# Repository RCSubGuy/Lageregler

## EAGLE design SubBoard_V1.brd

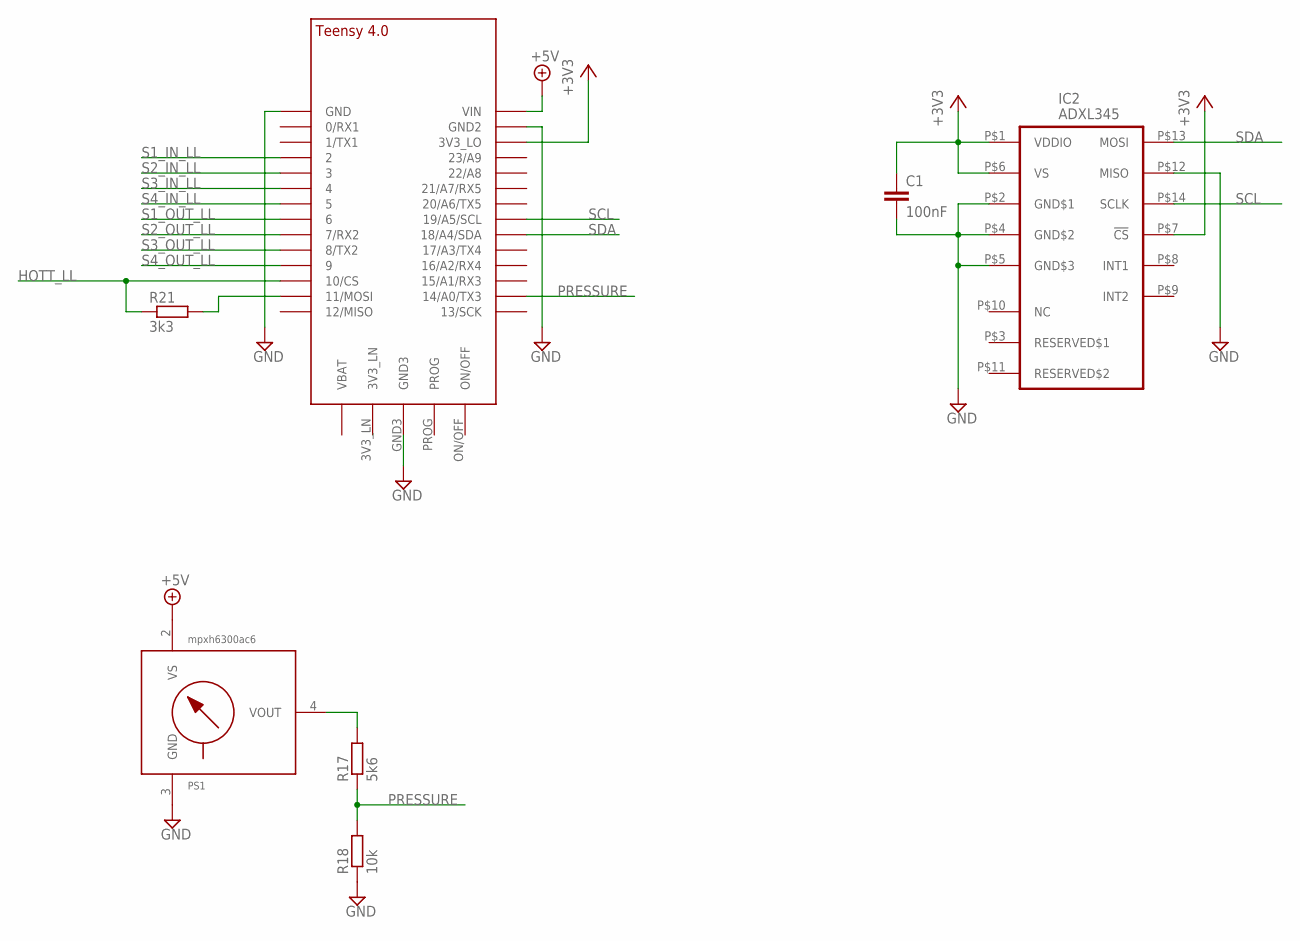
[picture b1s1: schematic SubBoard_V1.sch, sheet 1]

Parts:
C1: 100nF; C0805
IC2: ADXL345; LGA14
M1: TEENSY_4.0-BASIC
PS1: mpxh6300ac6; 482A
R17: 5k6; R0805
R18: 10k; R0805
R21: 3k3; R0805

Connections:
+3V3: C1.1, IC2.P$1 (VDDIO), IC2.P$6 (VS), IC2.P$7 (!CS), M1.3V3_LO; also elsewhere on the board
+5V: M1.VIN, PS1.2 (VS); also elsewhere on the board
GND: C1.2, IC2.P$2 (GND$1), IC2.P$4 (GND$2), IC2.P$5 (GND$3), IC2.P$12 (MISO), M1.GND, M1.GND2, M1.GND3, PS1.3 (GND), R18.1; also elsewhere on the board
HOTT_LL: M1.10/CS, R21.1; also elsewhere on the board
unnamed: PS1.4 (VOUT), R17.2
unnamed: M1.11/MOSI, R21.2
PRESSURE: M1.14/A0 (14/A0/TX3), R17.1, R18.2
S1_IN_LL: M1.2; also elsewhere on the board
S1_OUT_LL: M1.6; also elsewhere on the board
S2_IN_LL: M1.3/CANTX (3); also elsewhere on the board
S2_OUT_LL: M1.7 (7/RX2); also elsewhere on the board
S3_IN_LL: M1.4/CANRX (4); also elsewhere on the board
S3_OUT_LL: M1.8 (8/TX2); also elsewhere on the board
S4_IN_LL: M1.5; also elsewhere on the board
S4_OUT_LL: M1.9/CS (9); also elsewhere on the board
SCL: IC2.P$14 (SCLK), M1.19/A5/SCL
SDA: IC2.P$13 (MOSI), M1.18/A4/SDA

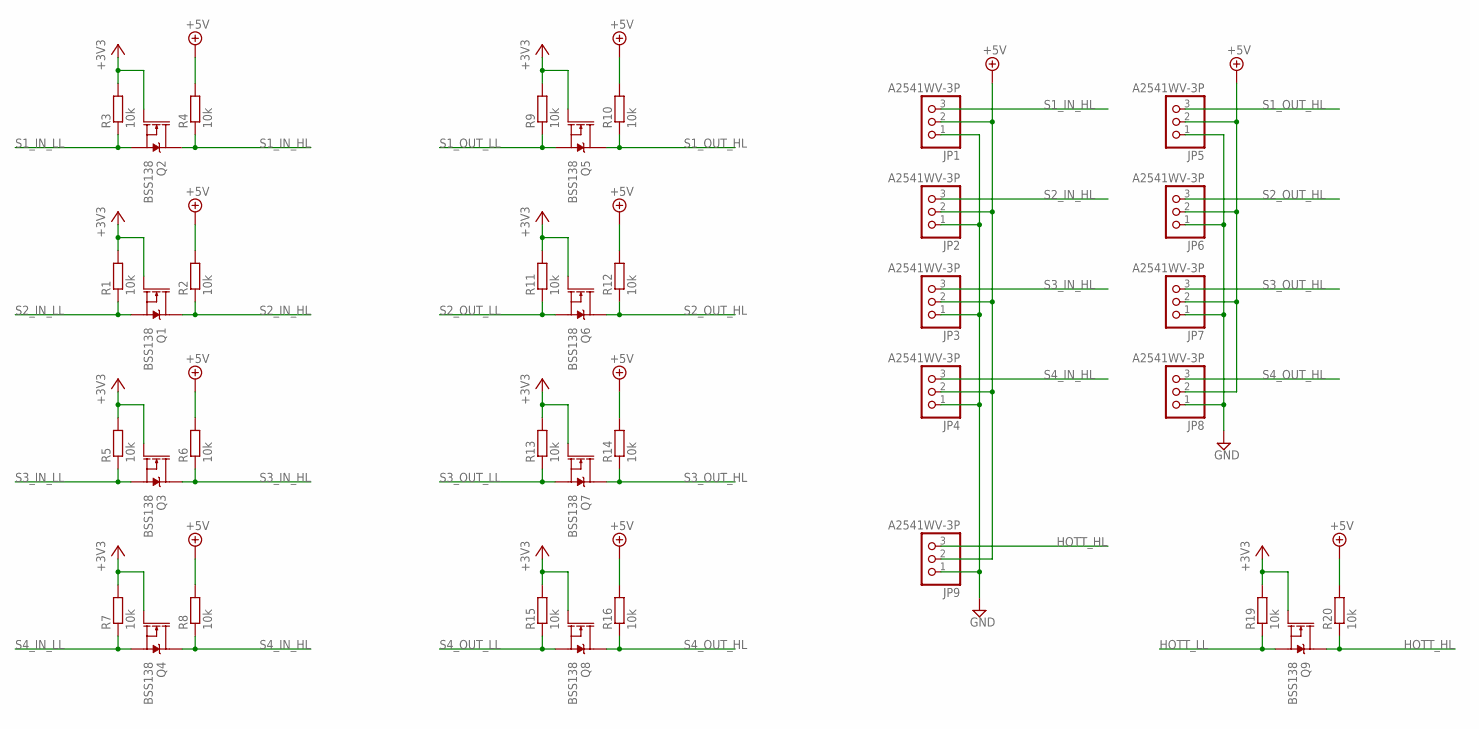
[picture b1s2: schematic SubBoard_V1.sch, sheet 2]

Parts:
JP1, JP2, JP3, JP4, JP5, JP6, JP7, JP8, JP9: A2541WV-3P; 1X03
Q1, Q2, Q3, Q4, Q5, Q6, Q7, Q8, Q9: BSS138; SOT23-3
R1, R2, R3, R4, R5, R6, R7, R8, R9, R10, R11, R12, R13, R14, R15, R16, R19, R20: 10k; R0603

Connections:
+3V3: Q1.1 (G), Q2.1 (G), Q3.1 (G), Q4.1 (G), Q5.1 (G), Q6.1 (G), Q7.1 (G), Q8.1 (G), Q9.1 (G), R1.2, R3.2, R5.2, R7.2, R9.2, R11.2, R13.2, R15.2, R19.2; also elsewhere on the board
+5V: JP1.2, JP2.2, JP3.2, JP4.2, JP5.2, JP6.2, JP7.2, JP8.2, JP9.2, R2.2, R4.2, R6.2, R8.2, R10.2, R12.2, R14.2, R16.2, R20.2; also elsewhere on the board
GND: JP1.1, JP2.1, JP3.1, JP4.1, JP5.1, JP6.1, JP7.1, JP8.1, JP9.1; also elsewhere on the board
HOTT_HL: JP9.3, Q9.3 (D), R20.1
HOTT_LL: Q9.2 (S), R19.1; also elsewhere on the board
S1_IN_HL: JP1.3, Q2.3 (D), R4.1
S1_IN_LL: Q2.2 (S), R3.1; also elsewhere on the board
S1_OUT_HL: JP5.3, Q5.3 (D), R10.1
S1_OUT_LL: Q5.2 (S), R9.1; also elsewhere on the board
S2_IN_HL: JP2.3, Q1.3 (D), R2.1
S2_IN_LL: Q1.2 (S), R1.1; also elsewhere on the board
S2_OUT_HL: JP6.3, Q6.3 (D), R12.1
S2_OUT_LL: Q6.2 (S), R11.1; also elsewhere on the board
S3_IN_HL: JP3.3, Q3.3 (D), R6.1
S3_IN_LL: Q3.2 (S), R5.1; also elsewhere on the board
S3_OUT_HL: JP7.3, Q7.3 (D), R14.1
S3_OUT_LL: Q7.2 (S), R13.1; also elsewhere on the board
S4_IN_HL: JP4.3, Q4.3 (D), R8.1
S4_IN_LL: Q4.2 (S), R7.1; also elsewhere on the board
S4_OUT_HL: JP8.3, Q8.3 (D), R16.1
S4_OUT_LL: Q8.2 (S), R15.1; also elsewhere on the board

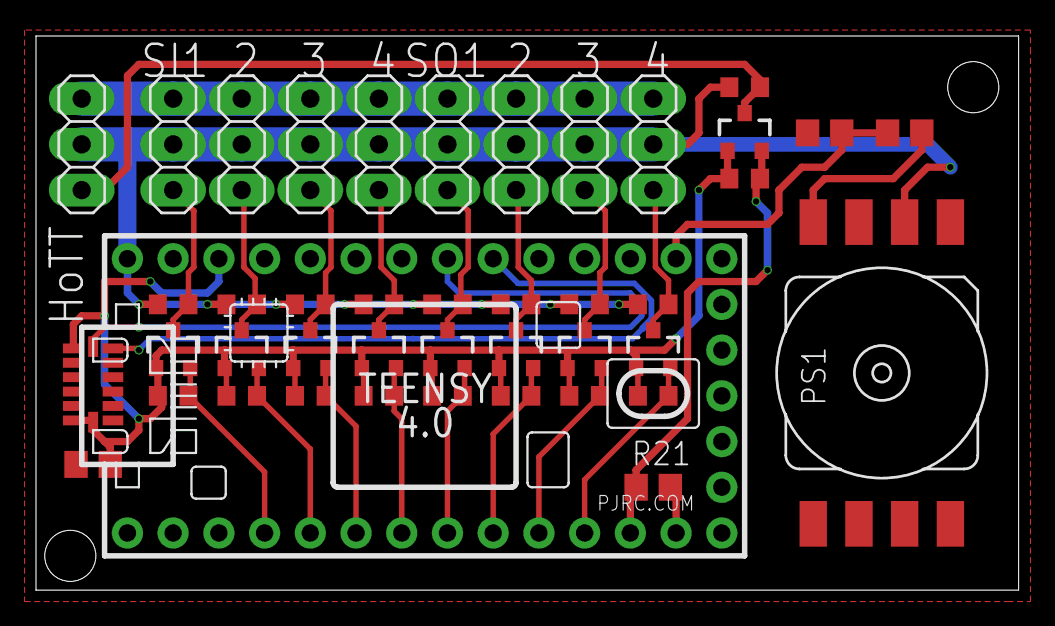
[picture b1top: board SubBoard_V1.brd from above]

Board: 2 copper layers, 54.6 x 30.8 mm, 43 parts (0 on the bottom side), 26 nets.

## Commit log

2021-09-03 code broken

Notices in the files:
parts and their libraries:
SparkFun-DiscreteSemi: Licensing: Creative Commons ShareAlike 4.0 International - https://creativecommons.org/licenses/by-sa/4.0
